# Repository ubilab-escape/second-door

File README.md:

**More notes on the implementation can be seen [here](
https://github.com/ubilab-escape/second-door/blob/master/docu/implementation.md)**

# Overview

- [Riddles](#Riddles)
  * [Stage 1 - Breaking the lock of the fusebox](#stage-1---breaking-the-lock-of-the-fusebox)
  * [Stage 2 - Restoring the power supply for the robot](#stage-2---restoring-the-power-supply-for-the-robot)
  * [Stage 3 - Breaking door by robot](#stage-3---breaking-door-by-robot)
- [Communication](#Communication)
- [How to](#How-to)
- [Future work](#future-work)

# Riddles

The main concept is visualized in the figure below.

<p align="center">Figure 1: Main concept<p align="center">

To open the second door, 3 puzzles must be solved. These puzzles are called Stages in the following. In case the participants get stuck they can ask for hints. The implemented hints can be seen [here](/docu/hints.md)

## Stage 1 - Breaking the lock of the fusebox

In the first stage the group has to crack the lock of the fusebox. A laser somewhere in the room is to be used. There is a lock on the fusebox which can only be opened when the laser beam is aimed at it. To do this, the group must use mirrors to divert the laser beam through the entire room. The 2 mirrors that can be used are mounted on a wall. This hides them, and the group must come up with the idea of using the mirrors.

The lock on the fusebox measures the laser beam. So that only this specific laser light can open the lock. The readout of the signal is done by the ESP32 inside the fusebox. The progress of this crack process is visualized with LEDs arranged in a circle. Once this color circle is closed, the microcontroller gives a signal to an actuator so that the lid of the fusebox opens. This completes the first stage.

<p align="center">Figure 2: Laser lock<p align="center">

To make it easier for the participants the laser warning symbol will be attached to the fusebox.

## Stage 2 - Restoring the power supply for the robot

Inside the fusebox two small "rewiring" riddles need to be solved . The following image shows the inside of the fusebox.

<p align="center">Figure 3: PCB fusebox<p align="center">

In the middle you can see an ESP32, which is responsible for the entire control of the PCB. Left to the ESP32, you can see two 5 pin headers (marked with 1). Both pairs must be connected using the attached jumper wire. The coding is hidden in the color marking of a soldered resistor which is right next to the connector. Above the ESP32 is a seven-segment display with 4 digits (marked with 2). With the help of potentiometers, a number can be set here (the year in which the faculty was founded). To the right of the ESP32 is the third riddle. Again the jumper wire needs to be connected in the right order. This time a binary number needs to be coded. Black wire indicates a zero and white wire a one. To get the right solution the participants have to sum up two hexadecimal numbers. The progress is visualized by an LED matrix on top of the PCB. In addition to the puzzles, there are other components on the PCB to confuse the group. When all the puzzles are solved, the robot inside the server room will get controllable from outside.

## Stage 3 - Breaking door by robot

It is just possible to open the door from inside by pushing a button with a small robot. Luckily the participants were able to repower the robot in the riddle before. The controller of the robot is placed on the other side of the room and a small window to look inside the server room is at the door. Therefore one participant has to guide the controlling one.

<p align="center">Figure 4: Robot<p align="center">

# Communication

To standardize the communication for all devices and make the handling as easy as possible we implemented the [MqttBase](https://github.com/JayWiz/MqttBase). Each device for the above riddles make use of this class. The class is embedded as sub repository.

# How to

The project is structured in four folder:

| Folder 	| Description 	|
|------	|---------------------|
[3D-files](https://github.com/ubilab-escape/second-door/tree/master/3D-files) | Contrains all .stp and .stl files for the designed cases |
[code](https://github.com/ubilab-escape/second-door/tree/master/code)| The .io files with all the code for each riddle |
[docu](https://github.com/ubilab-escape/second-door/tree/master/docu) | More detailed information about the implementation |
[pcb](https://github.com/ubilab-escape/second-door/tree/master/pcb) | The schematic and layout for the designed pcb |

The easiest way to work/compile/upload the code is to get [vs code](https://code.visualstudio.com/) and install [PlatfomIO](https://platformio.org/install/ide?install=vscode) as extension. The dependencies of each project are declared within the "lib_deps". The only missing part is the "wifi_secure.h" file which has to be created by the user. The file must contain:

```cpp
const char* ssid = "";
const char* password = "";
```

If you want to get the serial output for connection information define in the main.cpp file:

```cpp
#define DEBUG
```

# Future work

* robot controlled by ESP32 only
* cover/coating for pcb inside fusebox
* coating for fusebox

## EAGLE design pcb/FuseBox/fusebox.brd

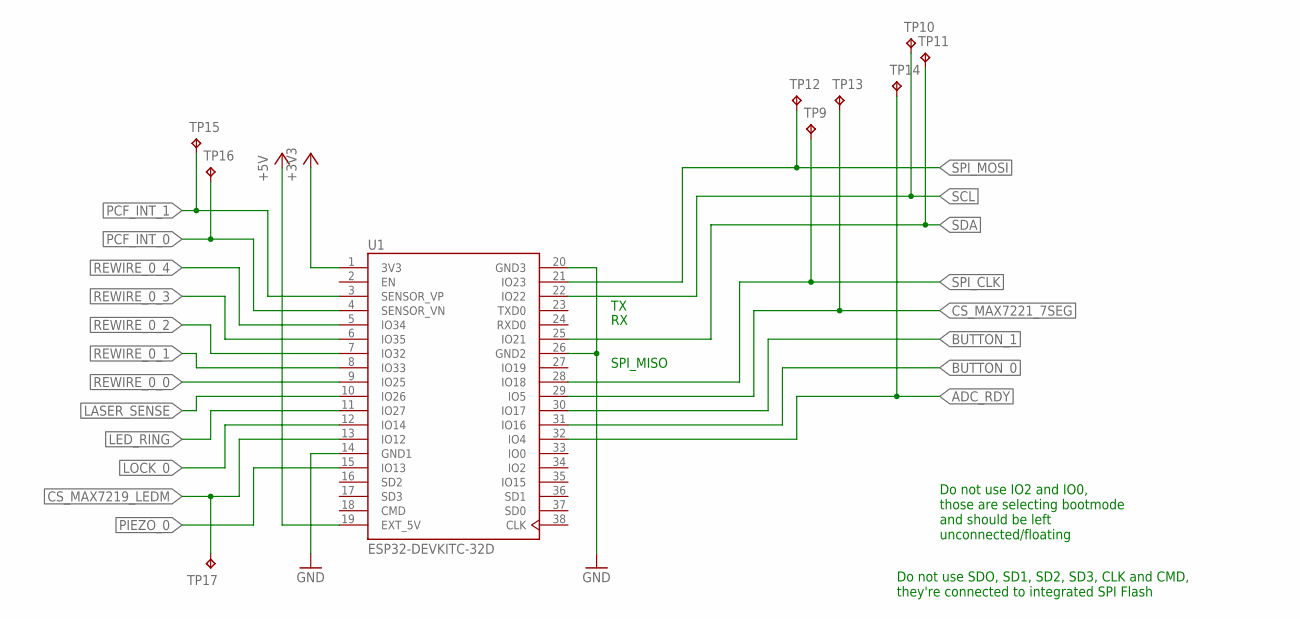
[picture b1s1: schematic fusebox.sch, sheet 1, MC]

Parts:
TP9, TP10, TP11, TP12, TP13, TP14, TP15, TP16, TP17: TPB1,27; B1,27
U1: ESP32-DEVKITC-32D; MODULE_ESP32-DEVKITC-32D

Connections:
+3V3: U1.1 (3V3); also elsewhere on the board
+5V: U1.19 (EXT_5V); also elsewhere on the board
ADC_RDY: TP14.TP, U1.32 (IO4); also elsewhere on the board
BUTTON_0: U1.31 (IO16); also elsewhere on the board
BUTTON_1: U1.30 (IO17); also elsewhere on the board
CS_MAX7219_LEDM: TP17.TP, U1.13 (IO12); also elsewhere on the board
CS_MAX7221_7SEG: TP13.TP, U1.29 (IO5); also elsewhere on the board
GND: U1.14 (GND1), U1.20 (GND3), U1.26 (GND2); also elsewhere on the board
LASER_SENSE: U1.10 (IO26); also elsewhere on the board
LED_RING: U1.11 (IO27); also elsewhere on the board
LOCK_0: U1.12 (IO14); also elsewhere on the board
PCF_INT_0: TP16.TP, U1.4 (SENSOR_VN); also elsewhere on the board
PCF_INT_1: TP15.TP, U1.3 (SENSOR_VP); also elsewhere on the board
PIEZO_0: U1.15 (IO13); also elsewhere on the board
REWIRE_0_0: U1.9 (IO25); also elsewhere on the board
REWIRE_0_1: U1.8 (IO33); also elsewhere on the board
REWIRE_0_2: U1.7 (IO32); also elsewhere on the board
REWIRE_0_3: U1.6 (IO35); also elsewhere on the board
REWIRE_0_4: U1.5 (IO34); also elsewhere on the board
SCL: TP10.TP, U1.22 (IO22); also elsewhere on the board
SDA: TP11.TP, U1.25 (IO21); also elsewhere on the board
SPI_CLK: TP9.TP, U1.28 (IO18); also elsewhere on the board
SPI_MOSI: TP12.TP, U1.21 (IO23); also elsewhere on the board

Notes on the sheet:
SPI_MISO
Do not use IO2 and IO0, those are selecting bootmode and should be left unconnected/floating
Do not use SDO, SD1, SD2, SD3, CLK and CMD, they're connected to integrated SPI Flash

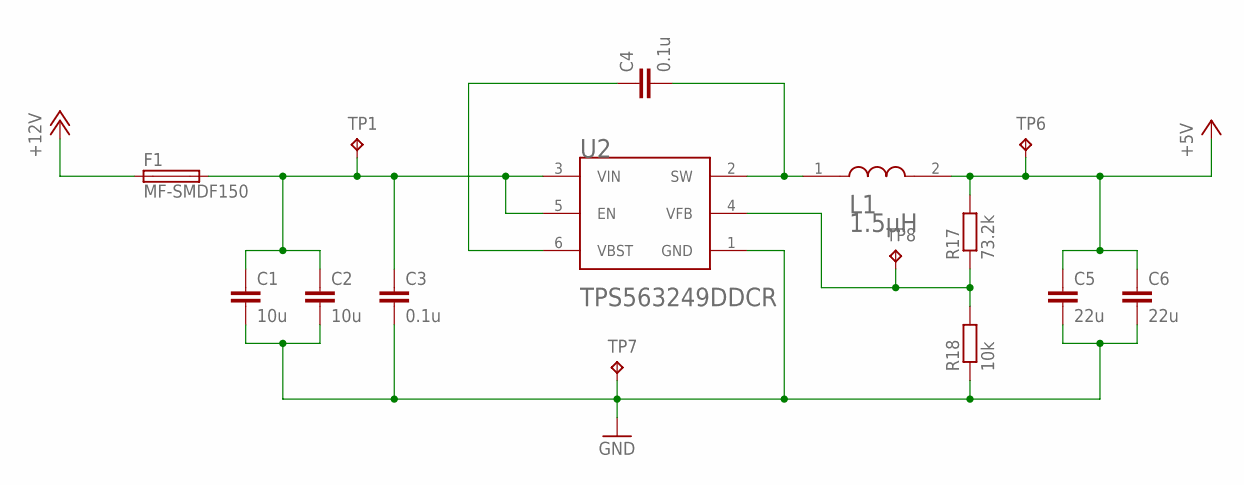
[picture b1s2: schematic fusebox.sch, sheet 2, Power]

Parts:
C1, C2: 10u; C1206
C3: 0.1u; C0603K
C4: 0.1u; C0603
C5, C6: 22u; C0603
F1: MF-SMDF150; MF-SMDF050
L1: BOURNS_SRN8040-1R5YBOURNS_SRN8040-1R5Y_0_0; BOURNS_SRN8040-1R5Y_0
R17: 73.2k; R0402
R18: 10k; R0201
TP1, TP6, TP7, TP8: TPB1,27; B1,27
U2: TEXAS_INSTRUMENTS_TPS563249DDCRTEXAS_INSTRUMENTS_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; TEXAS_INSTRUMENTS_TPS563249DDCR_0

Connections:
+5V: C5.1, C6.1, L1.2, R17.2, TP6.TP; also elsewhere on the board
+12V: F1.1; also elsewhere on the board
GND: C1.2, C2.2, C3.2, C5.2, C6.2, R18.1, TP7.TP, U2.1 (GND); also elsewhere on the board
unnamed: C1.1, C2.1, C3.1, F1.2, TP1.TP, U2.3 (VIN), U2.5 (EN)
unnamed: C4.1, U2.6 (VBST)
unnamed: C4.2, L1.1, U2.2 (SW)
unnamed: R17.1, R18.2, TP8.TP, U2.4 (VFB)

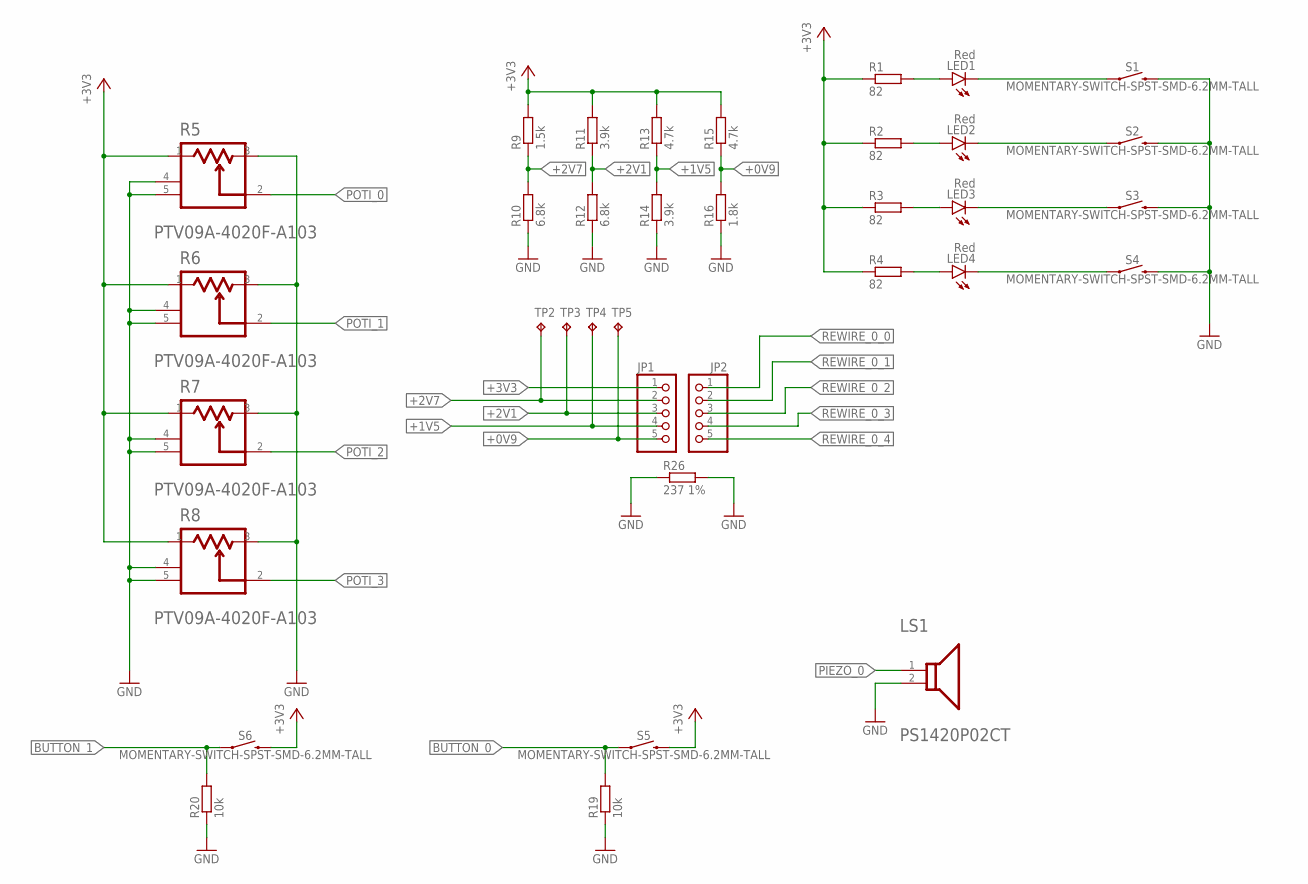
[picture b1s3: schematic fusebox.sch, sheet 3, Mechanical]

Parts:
JP1, JP2: PINHD-1X5; 1X05
LED1, LED2, LED3, LED4: Red; CHIP-LED0805
LS1: TDK_PS1420P02CTTDK_PS1420P02CT_0_0; TDK_PS1420P02CT_0
R1, R2, R3, R4: 82; R0805
R5, R6, R7, R8: BOURNS_PTV09A-4020F-A103BOURNS_PTV09A-4020F-A103_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; BOURNS_PTV09A-4020F-A103_0
R9: 1.5k; R0805
R10, R12: 6.8k; R0805
R11, R14: 3.9k; R0805
R13, R15: 4.7k; R0805
R16: 1.8k; R0805
R19, R20: 10k; R0805
R26: 237 1%; 0411/15
S1, S2, S3, S4, S5, S6: MOMENTARY-SWITCH-SPST-SMD-6.2MM-TALL; TACTILE_SWITCH_SMD_6.2MM_TALL
TP2, TP3, TP4, TP5: TPB1,27; B1,27

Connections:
+0V9: JP1.5, R15.1, R16.2, TP5.TP
+1V5: JP1.4, R13.1, R14.2, TP4.TP
+2V1: JP1.3, R11.1, R12.2, TP3.TP
+2V7: JP1.2, R9.1, R10.2, TP2.TP
+3V3: JP1.1, R1.1, R2.1, R3.1, R4.1, R5.1, R6.1, R7.1, R8.1, R9.2, R11.2, R13.2, R15.2, S5.B2 (2), S6.B2 (2); also elsewhere on the board
BUTTON_0: R19.2, S5.A2 (1); also elsewhere on the board
BUTTON_1: R20.2, S6.A2 (1); also elsewhere on the board
GND: LS1.2, R5.3, R5.4 (MNT_1), R5.5 (MNT_2), R6.3, R6.4 (MNT_1), R6.5 (MNT_2), R7.3, R7.4 (MNT_1), R7.5 (MNT_2), R8.3, R8.4 (MNT_1), R8.5 (MNT_2), R10.1, R12.1, R14.1, R16.1, R19.1, R20.1, R26.1, R26.2, S1.B2 (2), S2.B2 (2), S3.B2 (2), S4.B2 (2); also elsewhere on the board
unnamed: LED1.A, R1.2
unnamed: LED2.A, R2.2
unnamed: LED3.A, R3.2
unnamed: LED4.A, R4.2
unnamed: LED1.C, S1.A2 (1)
unnamed: LED2.C, S2.A2 (1)
unnamed: LED3.C, S3.A2 (1)
unnamed: LED4.C, S4.A2 (1)
PIEZO_0: LS1.1; also elsewhere on the board
POTI_0: R5.2; also elsewhere on the board
POTI_1: R6.2; also elsewhere on the board
POTI_2: R7.2; also elsewhere on the board
POTI_3: R8.2; also elsewhere on the board
REWIRE_0_0: JP2.1; also elsewhere on the board
REWIRE_0_1: JP2.2; also elsewhere on the board
REWIRE_0_2: JP2.3; also elsewhere on the board
REWIRE_0_3: JP2.4; also elsewhere on the board
REWIRE_0_4: JP2.5; also elsewhere on the board

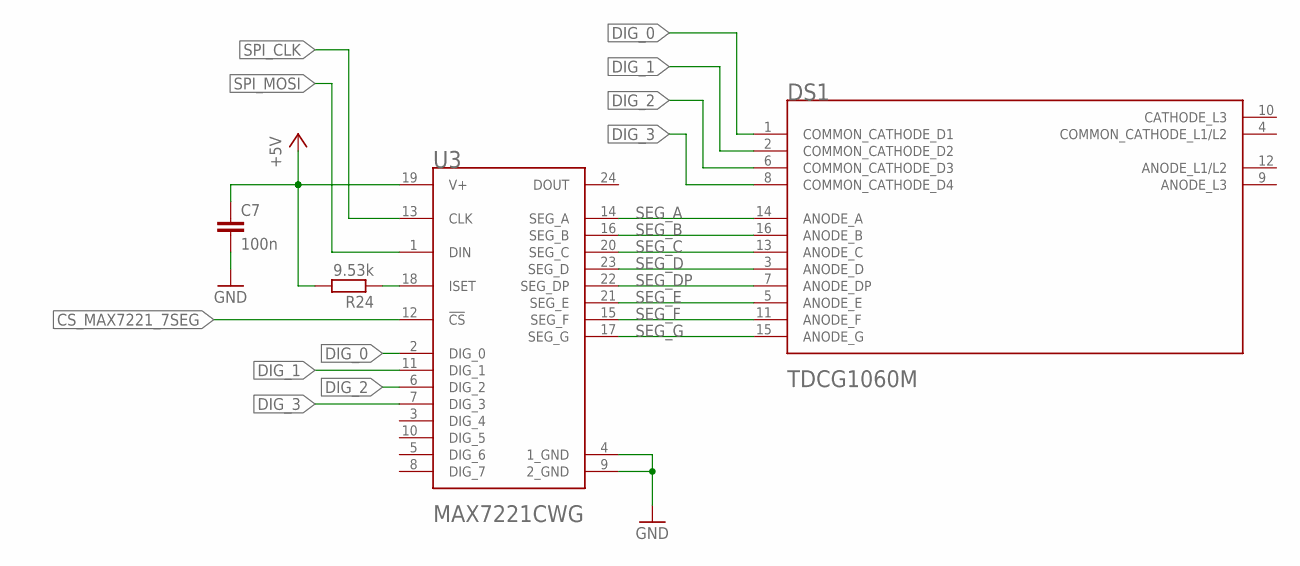
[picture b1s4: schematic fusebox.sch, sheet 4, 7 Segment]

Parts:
C7: 100n; C0805K
DS1: VISHAY_TDCG1060MVISHAY_TDCG1060M_0_0; VISHAY_TDCG1060M_0
R24: 9.53k; R0805
U3: MAXIM_ELECTRONICS_MAX7221CWGMAXIM_ELECTRONICS_MAX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; MAXIM_ELECTRONICS_MAX7221CWG_0

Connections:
+5V: C7.1, R24.2, U3.19 (V+); also elsewhere on the board
CS_MAX7221_7SEG: U3.12 (!CS!); also elsewhere on the board
DIG_0: DS1.1 (COMMON_CATHODE_D1), U3.2 (DIG_0)
DIG_1: DS1.2 (COMMON_CATHODE_D2), U3.11 (DIG_1)
DIG_2: DS1.6 (COMMON_CATHODE_D3), U3.6 (DIG_2)
DIG_3: DS1.8 (COMMON_CATHODE_D4), U3.7 (DIG_3)
GND: C7.2, U3.4 (1_GND), U3.9 (2_GND); also elsewhere on the board
unnamed: R24.1, U3.18 (ISET)
SEG_A: DS1.14 (ANODE_A), U3.14 (SEG_A)
SEG_B: DS1.16 (ANODE_B), U3.16 (SEG_B)
SEG_C: DS1.13 (ANODE_C), U3.20 (SEG_C)
SEG_D: DS1.3 (ANODE_D), U3.23 (SEG_D)
SEG_DP: DS1.7 (ANODE_DP), U3.22 (SEG_DP)
SEG_E: DS1.5 (ANODE_E), U3.21 (SEG_E)
SEG_F: DS1.11 (ANODE_F), U3.15 (SEG_F)
SEG_G: DS1.15 (ANODE_G), U3.17 (SEG_G)
SPI_CLK: U3.13 (CLK); also elsewhere on the board
SPI_MOSI: U3.1 (DIN); also elsewhere on the board

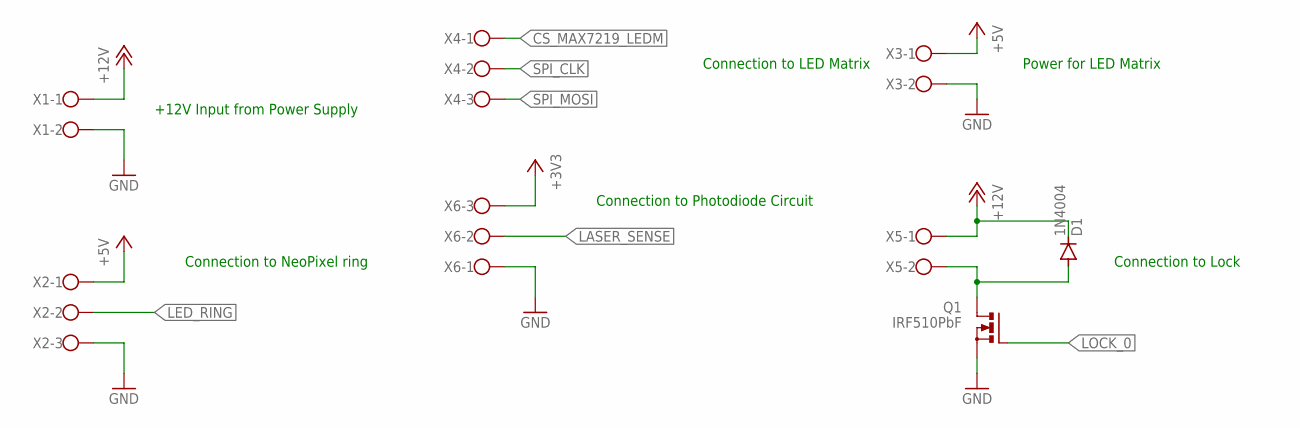
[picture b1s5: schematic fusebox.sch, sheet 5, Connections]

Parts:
D1: 1N4004; DO41-10
Q1: IRF510PbF; TO220BV
X1, X3, X5: W237-102
X2, X4, X6: W237-103

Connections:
+3V3: X6.3; also elsewhere on the board
+5V: X2.1, X3.1; also elsewhere on the board
+12V: D1.C, X1.1, X5.1; also elsewhere on the board
CS_MAX7219_LEDM: X4.1; also elsewhere on the board
GND: Q1.S, X1.2, X2.3, X3.2, X6.1; also elsewhere on the board
LASER_SENSE: X6.2; also elsewhere on the board
LED_RING: X2.2; also elsewhere on the board
unnamed 36: D1.A, Q1.D, X5.2; also elsewhere on the board
SPI_CLK: X4.2; also elsewhere on the board
SPI_MOSI: X4.3; also elsewhere on the board

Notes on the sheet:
+12V Input from Power Supply
Connection to LED Matrix
Power for LED Matrix
Connection to Photodiode Circuit
Connection to Lock
Connection to NeoPixel ring

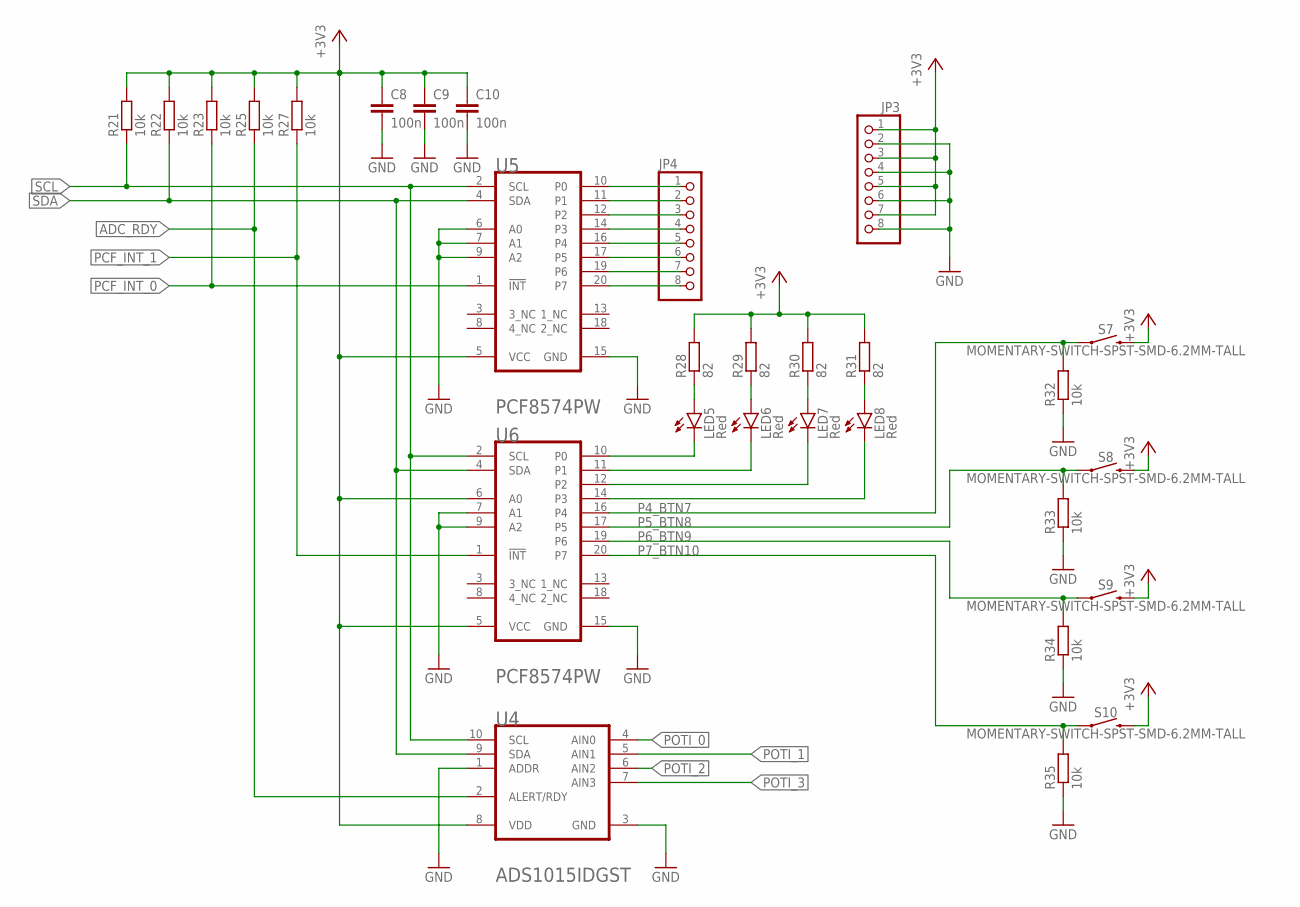
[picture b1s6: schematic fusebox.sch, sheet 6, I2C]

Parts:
C8, C9, C10: 100n; C0805K
JP3, JP4: PINHD-1X8; 1X08
LED5, LED6, LED7, LED8: Red; CHIP-LED0805
R21, R22, R23, R25, R27, R32, R33, R34, R35: 10k; R0805
R28, R29, R30, R31: 82; R0805
S7, S8, S9, S10: MOMENTARY-SWITCH-SPST-SMD-6.2MM-TALL; TACTILE_SWITCH_SMD_6.2MM_TALL
U4: TEXAS_INSTRUMENTS_ADS1015IDGSTTEXAS_INSTRUMENTS_A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; TEXAS_INSTRUMENTS_ADS1015IDGST_0
U5, U6: TEXAS_INSTRUMENTS_PCF8574PWTEXAS_INSTRUMENTS_PCF8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; TEXAS_INSTRUMENTS_PCF8574PW_0

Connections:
+3V3: C8.1, C9.1, C10.1, JP3.1, JP3.3, JP3.5, JP3.7, R21.2, R22.2, R23.2, R25.2, R27.2, R28.2, R29.2, R30.2, R31.2, S7.B2 (2), S8.B2 (2), S9.B2 (2), S10.B2 (2), U4.8 (VDD), U5.5 (VCC), U6.5 (VCC), U6.6 (A0); also elsewhere on the board
ADC_RDY: R25.1, U4.2 (ALERT/RDY); also elsewhere on the board
GND: C8.2, C9.2, C10.2, JP3.2, JP3.4, JP3.6, JP3.8, R32.1, R33.1, R34.1, R35.1, U4.1 (ADDR), U4.3 (GND), U5.6 (A0), U5.7 (A1), U5.9 (A2), U5.15 (GND), U6.7 (A1), U6.9 (A2), U6.15 (GND); also elsewhere on the board
unnamed: LED5.A, R28.1
unnamed: LED5.C, U6.10 (P0)
unnamed: LED6.A, R29.1
unnamed: LED6.C, U6.11 (P1)
unnamed: LED7.A, R30.1
unnamed: LED7.C, U6.12 (P2)
unnamed: JP4.1, U5.10 (P0)
unnamed: JP4.2, U5.11 (P1)
unnamed: JP4.3, U5.12 (P2)
unnamed: JP4.4, U5.14 (P3)
unnamed: JP4.5, U5.16 (P4)
unnamed: JP4.6, U5.17 (P5)
unnamed: JP4.7, U5.19 (P6)
unnamed: JP4.8, U5.20 (P7)
unnamed: LED8.A, R31.1
unnamed: LED8.C, U6.14 (P3)
P4_BTN7: R32.2, S7.A2 (1), U6.16 (P4)
P5_BTN8: R33.2, S8.A2 (1), U6.17 (P5)
P6_BTN9: R34.2, S9.A2 (1), U6.19 (P6)
P7_BTN10: R35.2, S10.A2 (1), U6.20 (P7)
PCF_INT_0: R23.1, U5.1 (!INT!); also elsewhere on the board
PCF_INT_1: R27.1, U6.1 (!INT!); also elsewhere on the board
POTI_0: U4.4 (AIN0); also elsewhere on the board
POTI_1: U4.5 (AIN1); also elsewhere on the board
POTI_2: U4.6 (AIN2); also elsewhere on the board
POTI_3: U4.7 (AIN3); also elsewhere on the board
SCL: R21.1, U4.10 (SCL), U5.2 (SCL), U6.2 (SCL); also elsewhere on the board
SDA: R22.1, U4.9 (SDA), U5.4 (SDA), U6.4 (SDA); also elsewhere on the board

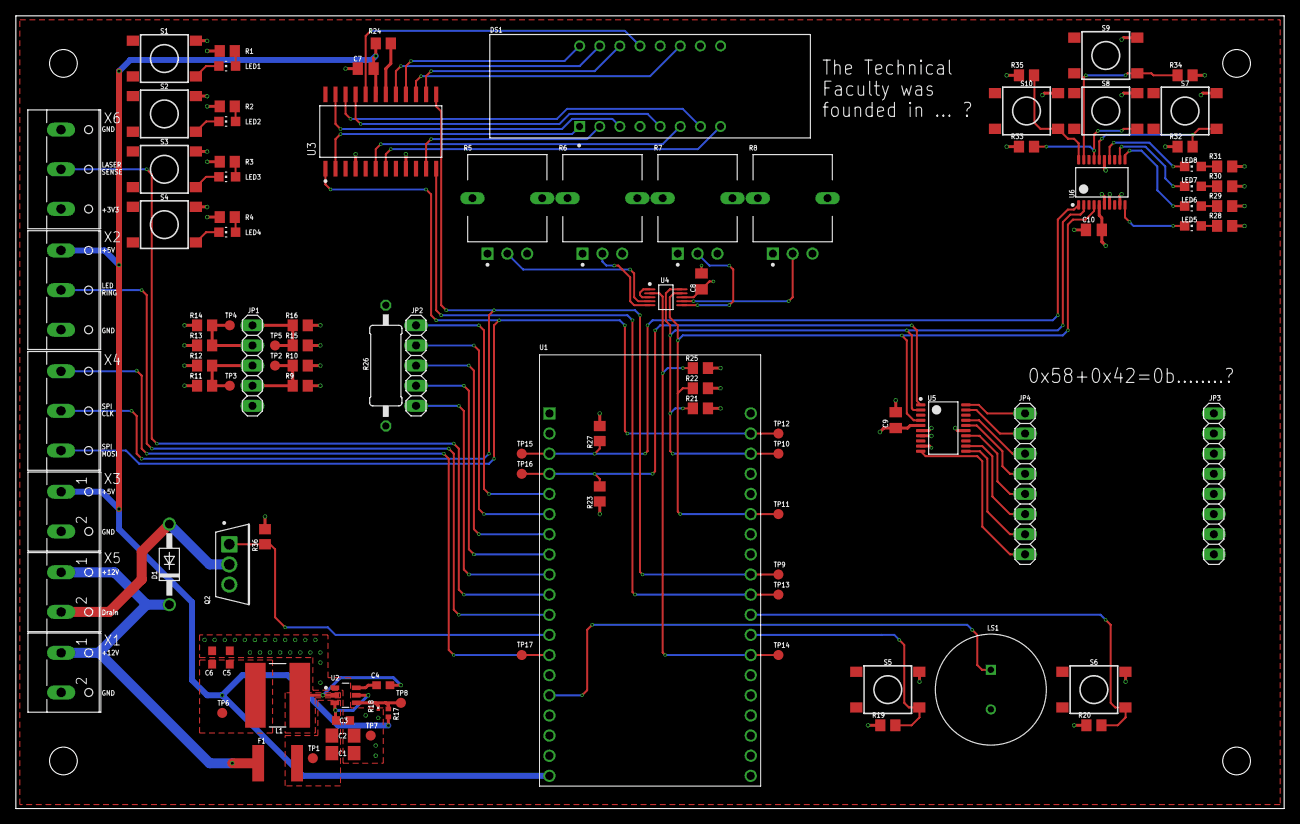
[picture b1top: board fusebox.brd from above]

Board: 2 copper layers, 160.0 x 100.0 mm, 103 parts (0 on the bottom side), 78 nets.

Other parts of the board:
Q2: INFINEON_IRLB8721PBFINFINEON_IRLB8721PBF_0_0; INFINEON_IRLB8721PBF_0
R36: 10k; R0805

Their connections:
GND: Q2.3, R36.1; also elsewhere on the board
LOCK_0: Q2.1, R36.2; also elsewhere on the board
unnamed 36: Q2.2; also elsewhere on the board

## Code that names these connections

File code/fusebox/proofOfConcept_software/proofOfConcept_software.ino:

#include "src/MAX7221/MAX7221.h"

#if CONFIG_FREERTOS_UNICORE
#define ARDUINO_RUNNING_CORE 0
#else
#define ARDUINO_RUNNING_CORE 1
#endif

#define MAX7221_CS 5 
#define MAX7219_CS 12

#define POTI_0 15
#define POTI_1 2 
#define POTI_2 0 
#define POTI_3 4 

#define PIEZO_0 13

#define BUTTON_0 16
#define BUTTON_1 17

#define LED_0 26 //2

#define LEDC_CHANNEL1 0
#define LEDC_RESOLUTION 8

#define REWIRE_0_1 25
#define REWIRE_0_2 33
#define REWIRE_0_3 32
#define REWIRE_0_4 35
#define REWIRE_0_5 34

#define LOCK_0 14

#define LED_RING 27

//#define LASER_SENSE 26

typedef enum tPuzzleState {INIT, SOLVED, NOT_SOLVED};

tPuzzleState puzzleStateRewiring0;
tPuzzleState puzzleStatePotis;


MAX7221 max1 = MAX7221(MAX7221_CS, 4);


uint16_t evaluatePotentiometer(uint8_t p_poti);
void setDisplay(uint16_t* p_displayData);

void TaskPotentiometerReadout(void *pvParameters);
void TaskWiringReadout(void *pvParameters);
void TaskPiezoButtonReadout(void *pvParameters);

void TaskControlPuzzleState(void *pvParameters);

void setup() {

  // TODO: Clean Setup
  // TODO: Implement MQTT Connection

  puzzleStateRewiring0 = INIT;
  puzzleStatePotis = INIT;

  Serial.begin(115200);
  Serial.println("Setup started");
  
  
  pinMode(BUTTON_0, INPUT);
  pinMode(BUTTON_1, INPUT);

  pinMode(LED_0, OUTPUT);

  // Init PWM Signals for Buzzers
  ledcSetup(LEDC_CHANNEL1, 2000, LEDC_RESOLUTION);
  ledcAttachPin(PIEZO_0, LEDC_CHANNEL1);

  // Init MAX7221 on SPI Bus
  max1.initMAX();

  Serial.println("Setup finished");

  // Attach Tasks
  xTaskCreatePinnedToCore(TaskControlPuzzleState, "TaskControlPuzzleState", 1024, NULL, 1, NULL, 0);
  xTaskCreatePinnedToCore(TaskPotentiometerReadout, "TaskPotentiometerReadout", 1024, NULL, 2, NULL, ARDUINO_RUNNING_CORE);
  xTaskCreatePinnedToCore(TaskWiringReadout, "TaskWiringReadout", 1024, NULL, 2, NULL, ARDUINO_RUNNING_CORE);
  xTaskCreatePinnedToCore(TaskPiezoButtonReadout, "TaskPiezoButtonReadout", 1024, NULL, 2, NULL, ARDUINO_RUNNING_CORE);
  

}

void loop() {
  // no code here!
  
}

void TaskPotentiometerReadout(void *pvParameters) {
  (void) pvParameters;
  for(;;) {
    uint16_t pValues[4];
    uint8_t potis[] = {POTI_0, POTI_1, POTI_2, POTI_3};
    for (int i = 0; i <= 3; i++) {
      pValues[i] = evaluatePotentiometer(potis[i], 0, 4095, 0, 9);
      Serial.print("Poti ");
      Serial.print(i);
      Serial.print(": ");
      Serial.println(pValues[i]);
    }
    max1.transferData(0x01, pValues[2]);
    max1.transferData(0x02, pValues[3]);

    if (pValues[0] == 4 && pValues[1] == 3 && pValues[2] == 2 && pValues[3] == 1) {
      Serial.println("Potis Solved!"); 
      puzzleStatePotis = SOLVED;
    } else {
      Serial.println("Potis Not solved!");
      puzzleStatePotis = NOT_SOLVED;
    }
    
    vTaskDelay(500);
  }
}

void TaskWiringReadout(void *pvParameters) {
  // TODO: Implement Wiring Puzzle
  (void) pvParameters;
  for(;;) {
    uint16_t rewiringValues0[5];
    uint16_t rewiringPins0[] = {REWIRE_0_1, REWIRE_0_2, REWIRE_0_3, REWIRE_0_4, REWIRE_0_5};
    for (int i = 0; i <=4; i++) {
      rewiringValues0[i] = analogRead(rewiringPins0[i]);
      rewiringValues0[i] = map(rewiringValues0[i], 0, 4095, 0, 33);
      // Serial.print("Pin " + String(i) + " : ");
      Serial.print("Rewiring 0_");
      Serial.print(i);
      Serial.print(": ");
      Serial.println(rewiringValues0[i]);
    }

    if (rewiringValues0[0] == 25 && rewiringValues0[1] == 18 && rewiringValues0[2] == 11 && rewiringValues0[3] == 33 && rewiringValues0[4] == 5) {
      Serial.println("Rewiring 0 solved!");
      puzzleStateRewiring0 = SOLVED;
    } else {
      Serial.println("Rewiring 0 not solved");
      puzzleStateRewiring0 = NOT_SOLVED;
    }

    vTaskDelay(500);
  }
}

void TaskControlPuzzleState(void *pvParameters) {
  (void) pvParameters;
  for(;;) {
    Serial.println("hey");
    if (puzzleStatePotis == SOLVED && puzzleStateRewiring0 == SOLVED) {
      Serial.println("All Puzzles Solved");
      digitalWrite(LED_0, HIGH);
    } else {
      digitalWrite(LED_0, LOW);
    }
    vTaskDelay(500);
  }
}

void TaskPiezoButtonReadout(void *pvParameters) {
  (void) pvParameters;
  for(;;) {
    // TODO: Debounce Buttons
    uint16_t buttonState1 = digitalRead(BUTTON_0);
    if(buttonState1) {
      float frequencies[] = {130.81, 164.81, 196.0, 246.94, 261.63, 246.94, 196.0, 164.81};
      for (int i = 0; i <= 7; i++) {
        ledcWriteTone(LEDC_CHANNEL1, frequencies[i]);
        vTaskDelay(250);
      } 
    } else {
      ledcWriteTone(LEDC_CHANNEL1, 0);
    }
    uint16_t buttonState2 = digitalRead(BUTTON_1);
    if(buttonState2) {
      // e 164.81
      // d# 155.56
      float frequencies[] = {164.81, 155.56, 164.81, 155.56, 123.47, 146.83, 130.81, 110};
      for (int i = 0; i <= 7; i++) {
        ledcWriteTone(LEDC_CHANNEL1, frequencies[i]);
        vTaskDelay(250);
      } 
    } else {
      ledcWriteTone(LEDC_CHANNEL1, 0);
    }
  }
}

uint16_t evaluatePotentiometer(uint8_t p_poti, uint16_t in_min, uint16_t in_max, uint16_t out_min, uint16_t out_max) {
  uint16_t value;
  value = analogRead(p_poti);
  value = map(value, in_min, in_max, out_min, out_max);
  return value;
}

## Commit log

2019-11-05 Update README.md
    Started with the documentation of our ideas in README
2019-11-05 add docu folder
2019-11-05 Update README.md
    Added image of room with laser
2019-11-05 Update README.md
    add link to laser sensor
2019-11-05 Update README.md
    Centered images and added captions
2019-11-06 README.md is under construction
2019-11-07 add pcb design idea
2019-11-07 Update README.md
    Added Description of Stage 2
2019-11-07 add different versions for stage 3
2019-11-07 add component table with estimated cost
2019-11-12 update README to selected ideas
2019-11-13 add docu for implementation
2019-11-13 add possible robot concept
2019-11-14 Added first version of .ino Sketch of ProofOfConcept for fusebox software
2019-11-15 Implemented functionality of buzzers, buttons, freeRTOS and potentiometers. Major Changes in code structure.
2019-11-22 Small fixes and improvements in software
2019-11-22 Initial Commit design-fusebox-hardware
2019-11-22 add ignore file
2019-11-22 ignore subfolder for ArduinoOutput
2019-11-22 Added .gitignore
2019-11-22 add ignore file from master
2019-11-26 little changes
2019-11-26 update robot and push button
2019-11-26 Added SPI communication with MAX7221
2019-11-26 add basic documentation for FuseBox
2019-11-26 remove .DS_Store file
2019-11-27 Added Header and cpp File for custom MAX7221 library, removed TM1637. Changed connection of Potis, implemented simple logic for Potis.
2019-11-28 Finished poc: Realized Functions: 1) Rewiring Puzzle 0 2) Potentiometer Puzzle 3) Visual Output of Potis with MAX7221 and 7 Segments 4) 2 Buzzers playing some sound 5) Scheduling of Tasks 6) Task whi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
2019-11-28 update to new room layout
2019-11-28 Changed Project structure
2019-11-28 update main concept and remove unused files
2019-11-28 update robot stage
2019-11-28 Added some new functions to schematic and layout
2019-11-28 fix pinout for esp in fusebox
2019-11-29 Changed software to use 4 digits on new display
2019-11-29 add few possible boxes
2019-12-04 RGB Sensor counts the hits of the sensor beam and shows the progress by changing the leds from red to green, counts down if no beam hits the sensor for more than one second. Up and down counting need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
2019-12-05 Major changes, currently problems with task scheduling (Task watchdog triggered. Following tasks did not reset the watchdog in time ..)
2019-12-05 Added new folder design-software with current software version. Major changes: Removed third party library for MAX72XX, add functionality to custom MAX7221 library. Changed IDE to platform.io
2019-12-05 Minor Change in .vscode config
2019-12-05 Changed Serial Logs and removed Debug of WiringPuzzle
2019-12-06 Added clang-format
2019-12-06 add 3D test file for led ring housing
2019-12-06 Added Code fragments of Thomas: LED-Ring and rgbSensor
2019-12-06 Change of c_cpp_properties.json
2019-12-07 add laserLock_Laser_sensor
2019-12-09 implemented down counting of leds
2019-12-09 Modified .gitignore
2019-12-09 Added second PCF8574 with some buttons and LEDs, finished I2C circuits, finished MAX7221 circuit, rearranged sheets, minor changes in circuit.
2019-12-09 split laser and laser sensor
2019-12-11 add bink if puzzle lock is broken, fixd bug: ring did not become green if more than one minute ther was no detection
2019-12-12 Some big changes
2019-12-13 remove .prt file and add -stp instead
2019-12-13 add case for pushButton
2019-12-13 modify push button case
2019-12-18 add communication folder
2019-12-18 Further work on PCB
2019-12-18 add fuse box 3D files
2019-12-18 Further work on PCB, almost done. Just have to route I2C and SPI lanes.
2019-12-19 Finished 1st version of layout
2019-12-19 added pc mounting holes
2019-12-19 change to 2 layer
2019-12-19 Started to implement thomis changes
2019-12-19 connected
2019-12-19 Implemented Thomis work with the LED Ring and Laser sensor
2019-12-20 minor GND plane fixes
2019-12-20 Added Debug LED
2019-12-27 sort 3D files to folder
2019-12-27 add laser case
2020-01-08 add wall mount
2020-01-08 add mounting for LED ring for fuseBox
2020-01-08 test commit
2020-01-08 remove test file
2020-01-08 change laserCase to reduced printing time
2020-01-08 add json format decoding and encoding
2020-01-08 add fusebox case and laser case
2020-01-08 change communication structure
2020-01-08 reopen documentation branch
2020-01-09 working but without RTOS
2020-01-09 use task for controll
2020-01-09 add NeoPixel lib
2020-01-09 add Robot class
2020-01-09 Changed LED matrix library and some other stuff
2020-01-09 Changed Size of LED Panel: Danke MAXgit add *1git add *1!
2020-01-09 controller can change robot color
2020-01-14 minor change
2020-01-14 Adapted Software to new Hardware various changes
2020-01-15 subscribe and json
2020-01-15 Minor changes
2020-01-15 add 3D step and stl files
2020-01-16 basic push_button code
2020-01-17 just commit to merge to master
2020-01-17 add example for broker(8266) and client
2020-01-17 Solution for integer division by zero problem found, not longer using map(..) function!
2020-01-17 add communication.h
2020-01-17 Added WiFi function
2020-01-20 add common_com
2020-01-20 remove second communication file
2020-01-20 add class wrapper for mqtt
2020-01-20 wrapper class causes Guru Meditation Error: Core 1 panic'ed
2020-01-20 Corrected Initialization of PubSubClient and WiFiClient
2020-01-20 rename and split to mqtt_base class
2020-01-20 testing mqtt_bast for laser --> not working right now
2020-01-20 add MqttBase class
2020-01-21 rename base folder
2020-01-21 add subrepo
2020-01-21 made riddles all parallel
2020-01-21 Added Submodule
2020-01-21 add submodule
2020-01-21 update laser communication
2020-01-21 Small change in Fonts
2020-01-21 make use of mqtt_client_name from base class
2020-01-21 MQTT subscribe and callback are working now with MqttBase class
2020-01-21 switch button on an off via mqtt
2020-01-21 small changes
2020-01-21 small easy serial uni communication
2020-01-21 switch button on and off oover mqtt, set retain bit if solved, send status active if trigger on is set, send status inactive if trigger off is set
2020-01-21 add function prototyps
2020-01-21 Serial print changed to Debug
2020-01-21 Moved Serial debug
2020-01-21 changed Status to capital letter in json
2020-01-21 set duty cycle of laser pin to zero in off state, fixed bug in init of rgb
2020-01-21 serial sucks
2020-01-21 Changed Task Deletions
2020-01-21 revert to previous branch
2020-01-22 make use of pin instead of serial
2020-01-22 Working right now with checking puzzle state from server, sometimes there are still crashes
2020-01-22 New MqttBase, refresh of WiFi at reboot is working now. Software seems stable now. Further improvements are possible, but this status is good for presentation on Friday
2020-01-22 Modified travis config
2020-01-22 Changed directory
2020-01-22 Removed pull of submodule
2020-01-22 Added Fake wifi_secure.h
2020-01-22 Changed submodule stuff
2020-01-22 removed private key
2020-01-22 Update README.md
    Added travis badge
2020-01-22 Added Slack Notification
2020-01-22 Added multiple build jobs
2020-01-22 Changed libDeps
2020-01-22 udated submodule
2020-01-22 update and cleaned
2020-01-22 Corrected delays in publish Function
2020-01-22 rename
2020-01-23 add submodule again to push_button
2020-01-23 deleted string lib, deleted print in callback, updated mqtt_base, sends status inactive at startup
2020-01-23 Added robotESP and push_button to Travis CI
2020-01-23 Modified platform.ini of push_button and robotESP, added lib_deps for ArduinoJson and PubSubClient
2020-01-23 robotPS2 added to travis build
2020-01-23 add FreeRTOS to lib_deps
2020-01-23 correct name
2020-01-23 add hints to docu
2020-01-24 remove .rtf file
2020-01-29 hear to on and ON - same for off
2020-01-29 add a few pictures - description is needed
2020-01-29 Working on porblem, changed logic of MQTT
2020-01-29 Updated Submodules
2020-01-29 publish status with data
2020-01-29 add case insensivity
2020-01-29 Its working now, finally
2020-01-29 Added new MqttBase to working fusebox
2020-01-30 Tried to embed pdf of fusebox
2020-01-30 Added .png files and removed pdf files, included them to implementation.md
2020-01-30 Changed size of schematics
2020-01-30 Continued work on documentation in implementation
2020-01-30 add table of content
2020-02-04 add debug information
2020-02-04 new mounting files for PS2 controller
2020-02-04 update to old subrepos
2020-02-04 Changed LED RIng behaviour, changed led matrix behaviour
2020-02-05 more robust design for ps2 mounting
2020-02-05 Changed Adafruit NeoPixel Library to Neopixel bus library, LED ring is not flickering anymore
2020-02-05 removed old folders
2020-02-07 add battery publish
2020-02-08 read out low voltage and ESP power supply
2020-02-08 start with robot off
2020-02-08 Added open Lock at trigger:off
2020-02-11 Added Poster
2020-02-14 correct battery status output
2020-02-21 Changed .gitignore in design-software
2020-02-21 Untrack files in .gitignore
2020-02-21 Modified .gitignore file to entirely ignore .vscode folder
2020-02-28 merged master into documentation
2020-02-28 add comments in Button and Laser
2020-02-28 Added Comments to design_software and updated submodules
2020-02-28 this project was amazing :P - we hope for a good grade :)
2020-02-28 clean and comment robot
2020-02-28 blablablalbs

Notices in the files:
parts and their libraries:
SparkFun-Switches: Licensing: Creative Commons ShareAlike 4.0 International - https://creativecommons.org/licenses/by-sa/4.0
